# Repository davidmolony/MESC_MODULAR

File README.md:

# MESC_MODULAR
This is a repo for an experimental through hole stage and power driver

For use either with Pinski control board, or with any control stage - Lebowski, nucleo breakouts and jumper wires, Infineon breakout boards... whatever.

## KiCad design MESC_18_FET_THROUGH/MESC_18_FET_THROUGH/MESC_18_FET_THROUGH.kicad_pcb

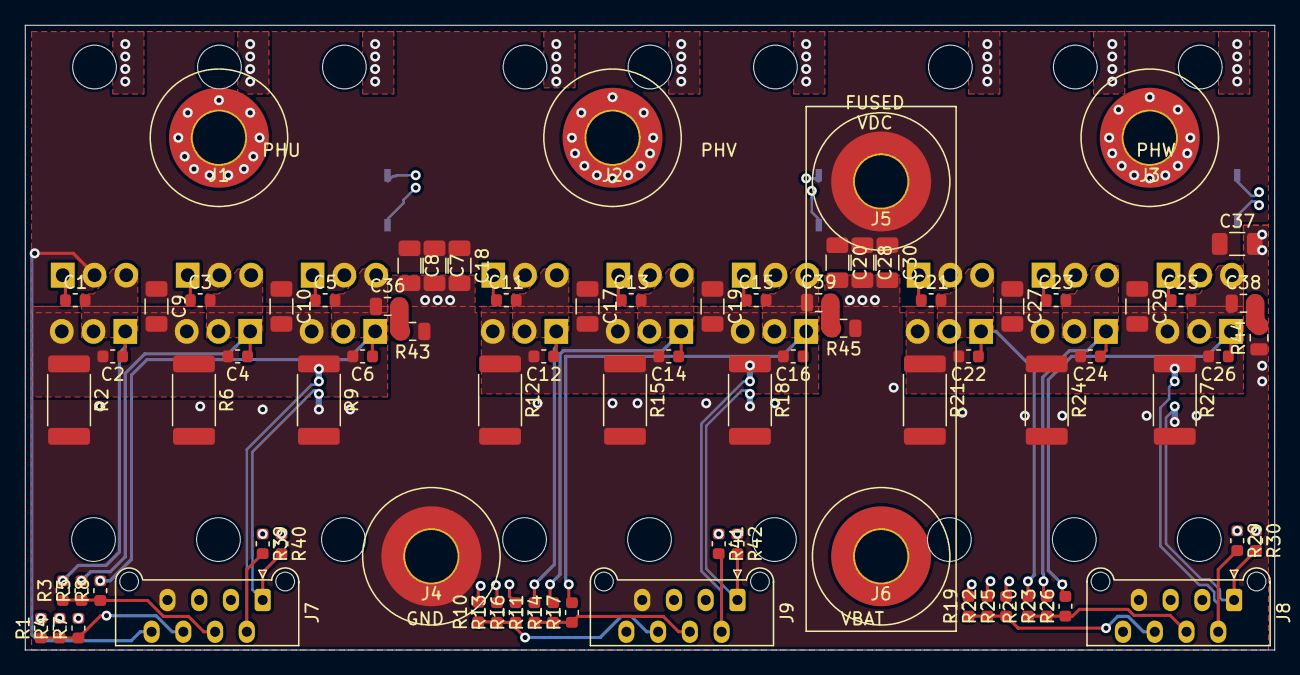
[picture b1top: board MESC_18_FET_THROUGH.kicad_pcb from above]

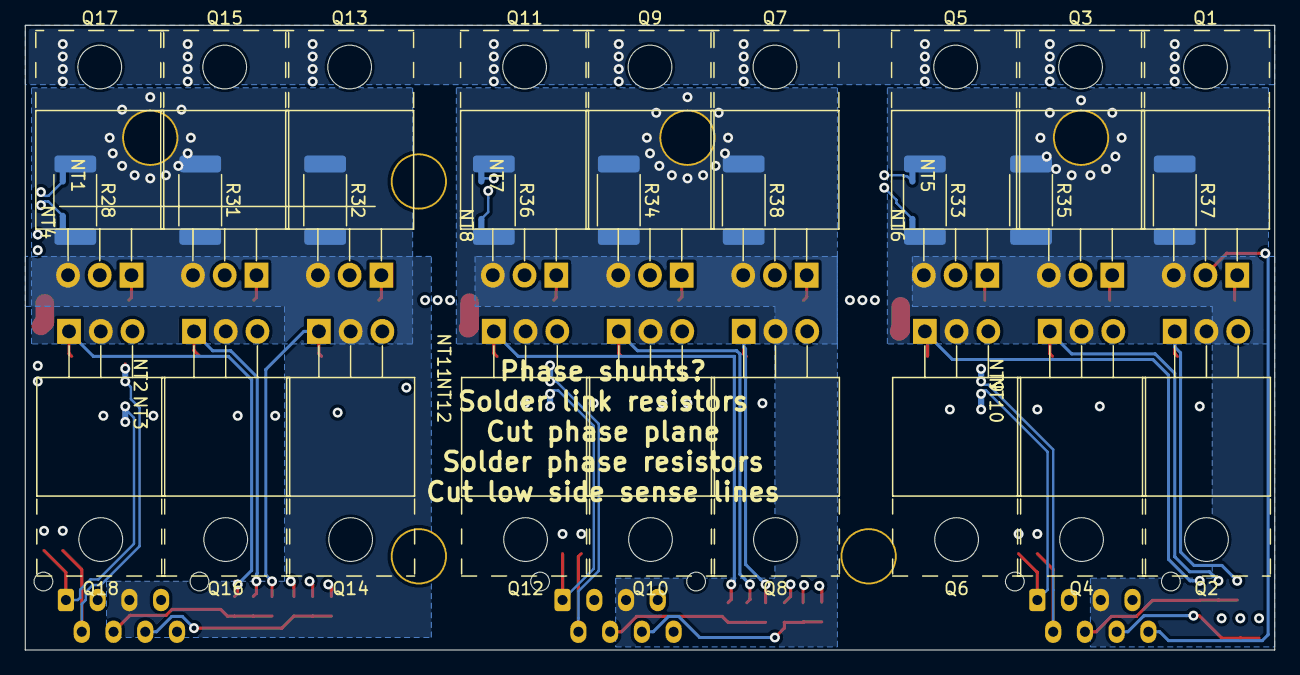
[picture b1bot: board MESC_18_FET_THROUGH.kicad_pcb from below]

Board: 4 copper layers, 100.0 x 50.0 mm, 118 parts (39 on the bottom side), 47 nets.

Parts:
C1, C2, C3, C4, C5, C6, C11, C12, C13, C14, C15, C16, C21, C22, C23, C24, C25, C26: DNF 4.7nF 25V; C_0603_1608Metric
C7, C8, C9, C10, C17, C18, C19, C20, C27, C28, C29, C30, C37: 1uF 100V; C_1206_3216Metric
C36, C38, C39: 4.7nF 100V; C_0805_2012Metric
J1, J2, J3, J4, J5, J6: M4 screw; Wuerth_Redcube_M4
J7, J8, J9: Conn_01x08_Male; Molex_Picoflex_90325-0008_2x04_P1.27mm_Vertical
NT1, NT2, NT3, NT4, NT5, NT6, NT7, NT8, NT9, NT10, NT11, NT12: Net-Tie_2; NetTie-2_SMD_Pad0.5mm
Q1, Q2, Q3, Q4, Q5, Q6, Q7, Q8, Q9, Q10, Q11, Q12, Q13, Q14, Q15, Q16, Q17, Q18: STP150N10F7; TO-220-3_Horizontal_TabUp
R1, R3, R4, R5, R7, R8, R10, R11, R13, R14, R16, R17, R19, R20, R22, R23, R25, R26: 4.7R; R_0603_1608Metric
R2, R6, R9, R12, R15, R18, R21, R24, R27, R28, R31, R32, R33, R34, R35, R36, R37, R38: 0R001; R_2512_6332Metric
R29, R30, R39, R40, R41, R42: DNF 100R; R_0603_1608Metric
R43, R44, R45: 2R2; R_0805_2012Metric

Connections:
+VDC: C7.1, C8.1, C9.1, C10.1, C17.1, C18.1, C19.1, C20.1, C27.1, C28.1, C29.1, C30.1, C37.1, J5.1, J7.8, Q1.2, Q3.2, Q5.2, Q7.2, Q9.2, Q11.2, Q13.2, Q15.2, Q17.2
/ISUH+: NT5.2, R39.1
/ISUH-: NT6.2, R40.1
/ISVH+: NT7.2, R41.1
/ISVH-: NT8.2, R42.1
/ISWH+: NT1.2, R29.1
/ISWH-: NT4.2, R30.1
GND: C7.2, C8.2, C18.2, C20.2, C28.2, C30.2, C37.2, J4.1, J7.7, J8.7, J9.7, NT3.2, NT10.2, NT12.2, R2.2, R6.2, R9.2, R12.2, R15.2, R18.2, R21.2, R24.2, R27.2, R43.1, R44.1, R45.1
ISU+: J7.2, NT9.2, R39.2
ISU-: J7.1, NT10.1, R40.2
ISV+: J9.2, NT11.2, R41.2
ISV-: J9.1, NT12.1, R42.2
ISW+: J8.2, NT2.2, R29.2
ISW-: J8.1, NT3.1, R30.2
unnamed: C1.1, Q1.1, R1.2
unnamed: C2.1, Q2.1, R3.2
unnamed: C3.1, Q3.1, R4.2
unnamed: C4.1, Q4.1, R5.2
unnamed: C5.1, Q5.1, R7.2
unnamed: C6.1, Q6.1, R8.2
unnamed: C11.1, Q7.1, R10.2
unnamed: C12.1, Q8.1, R11.2
unnamed: C13.1, Q9.1, R13.2
unnamed: C14.1, Q10.1, R14.2
unnamed: C15.1, Q11.1, R16.2
unnamed: C16.1, Q12.1, R17.2
unnamed: C21.1, Q13.1, R19.2
unnamed: C22.1, Q14.1, R20.2
unnamed: C23.1, Q15.1, R22.2
unnamed: C24.1, Q16.1, R23.2
unnamed: C25.1, Q17.1, R25.2
unnamed: C26.1, Q18.1, R26.2
unnamed: C36.2, R43.2
unnamed: C38.2, R44.2
unnamed: C39.2, R45.2
UGH: J7.6, R1.1, R4.1, R7.1
UGL: J7.4, R3.1, R5.1, R8.1
USOURCE: C2.2, C4.2, C6.2, C9.2, C10.2, J7.3, NT9.1, Q2.3, Q4.3, Q6.3, R2.1, R6.1, R9.1
USWITCH: C1.2, C3.2, C5.2, C36.1, J1.1, J7.5, NT5.1, NT6.1, Q1.3, Q2.2, Q3.3, Q4.2, Q5.3, Q6.2, R33.1, R33.2, R35.1, R35.2, R37.1, R37.2
VGH: J9.6, R10.1, R13.1, R16.1
VGL: J9.4, R11.1, R14.1, R17.1
VSOURCE: C12.2, C14.2, C16.2, C17.2, C19.2, J9.3, NT11.1, Q8.3, Q10.3, Q12.3, R12.1, R15.1, R18.1
VSWITCH: C11.2, C13.2, C15.2, C39.1, J2.1, J9.5, NT7.1, NT8.1, Q7.3, Q8.2, Q9.3, Q10.2, Q11.3, Q12.2, R34.1, R34.2, R36.1, R36.2, R38.1, R38.2
WGH: J8.6, R19.1, R22.1, R25.1
WGL: J8.4, R20.1, R23.1, R26.1
WSOURCE: C22.2, C24.2, C26.2, C27.2, C29.2, J8.3, NT2.1, Q14.3, Q16.3, Q18.3, R21.1, R24.1, R27.1
WSWITCH: C21.2, C23.2, C25.2, C38.1, J3.1, J8.5, NT1.1, NT4.1, Q13.3, Q14.2, Q15.3, Q16.2, Q17.3, Q18.2, R28.1, R28.2, R31.1, R31.2, R32.1, R32.2

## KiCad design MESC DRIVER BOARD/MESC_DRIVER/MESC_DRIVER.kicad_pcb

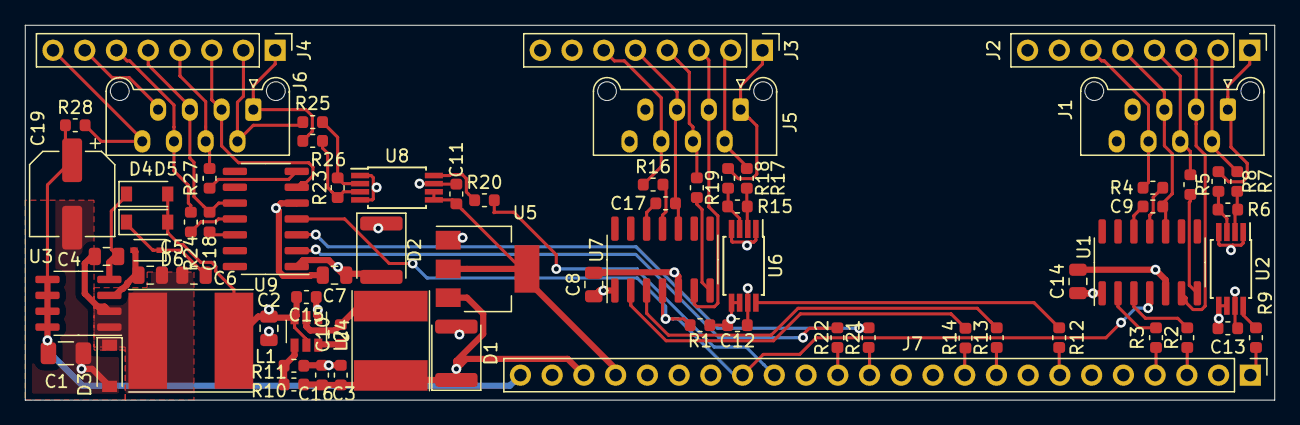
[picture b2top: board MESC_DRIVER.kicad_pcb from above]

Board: 4 copper layers, 100.0 x 30.0 mm, 71 parts (0 on the bottom side), 65 nets.

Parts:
C1: C_Small; C_1206_3216Metric
C2, C4, C5, C6, C7, C8, C14: C_Small; C_0805_2012Metric
C3, C9, C10, C11, C12, C13, C15, C16, C17, C18: C_Small; C_0603_1608Metric
C19: CP_Small; CP_Elec_6.3x7.7
D1, D2: D_TVS; D_1812_4532Metric
D3, D4, D5: D_Small; D_SOD-123
D6: D_Zener_Small; D_SOD-323
J1, J5, J6: Conn_01x08_Male; Molex_Picoflex_90325-0008_2x04_P1.27mm_Vertical
J2, J3, J4: Conn_01x08_Male; PinHeader_1x08_P2.54mm_Vertical
J7: Conn_01x24_Male; PinHeader_1x24_P2.54mm_Vertical
L1: L_Small; L_Taiyo-Yuden_NR-80xx_HandSoldering
L2: L_Small; L_Taiyo-Yuden_NR-60xx_HandSoldering
R1, R2, R3, R4, R5, R6, R7, R8, R9, R10, R11, R12, R13, R14, R15, R16, R17, R18, R19, R20, R21, R22, R23, R24, R25, R26, R27, R28: R_Small; R_0603_1608Metric
U1, U7, U9: 2EDL23N06; SOIC-14_3.9x8.7mm_P1.27mm
U2, U6, U8: INA240A2PW; TSSOP-8_4.4x3mm_P0.65mm
U3: VIPer22AS; SOIC-8_3.9x4.9mm_P1.27mm
U4: TPS563200; SOT-23-6
U5: LM1117-3.3; SOT-223-3_TabPin2

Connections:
+3V3: C11.1, C12.1, C13.1, J7.21, R1.2, U2.5, U2.6, U5.2, U6.5, U6.6, U8.5, U8.6
+5V: C3.1, C16.1, D1.1, J7.22, L2.1, R10.1, U5.3
+15V: C2.1, C7.1, C8.1, C14.1, C15.2, D2.2, D4.2, D5.2, J7.23, L1.1, U1.1, U4.3, U4.5, U7.1, U9.1
+BATT: J4.8, J6.8, R28.2
+VDC: C1.1, C19.1, J7.24, R28.1, U3.5, U3.6, U3.7, U3.8
GND: C1.2, C2.2, C3.2, C7.2, C8.2, C11.2, C12.2, C13.2, C14.2, C15.1, C16.2, C19.2, D1.2, D2.1, D3.2, J4.7, J6.7, J7.2, J7.8, J7.15, J7.20, R11.2, U1.5, U2.1, U2.4, U2.7, U4.1, U5.1, U6.1, U6.4, U6.7, U7.5, U8.1, U8.4, U8.7, U9.5
HINU: J7.4, R3.2
HINV: J7.10, R14.2
HINW: J7.14, R22.2
HOU: J1.6, J2.6, R4.1
HOV: J3.6, J5.6, R16.1
HOW: J4.6, J6.6, R24.1
IU+: J1.2, J2.2, R7.2
IU-: J1.1, J2.1, R8.1
IV+: J3.2, J5.2, R17.2
IV-: J3.1, J5.1, R18.1
IW+: J4.2, J6.2, R25.2
IW-: J4.1, J6.1, R26.1
LINU: J7.3, R2.1
LINV: J7.9, R13.1
LINW: J7.13, R21.1
LOU: J1.4, J2.4, R5.1
LOV: J3.4, J5.4, R19.1
LOW: J4.4, J6.4, R27.1
unnamed: C4.1, D4.1, U3.4
unnamed: C4.2, C5.2, C6.2, D3.1, L1.2, U3.1, U3.2
unnamed: C6.1, D5.1, D6.1
unnamed: C9.1, U1.12
unnamed: C10.1, U4.6
unnamed: C10.2, L2.2, U4.2
unnamed: C17.1, U7.12
unnamed: C18.1, U9.12
unnamed: R2.2, U1.3
unnamed: R3.1, U1.2
unnamed: R4.2, U1.11
unnamed: R5.2, U1.7
unnamed: R6.1, R8.2, U2.3
unnamed: R6.2, R7.1, U2.2
unnamed: R9.1, U2.8
unnamed: R10.2, R11.1, U4.4
unnamed: R12.1, U6.8
unnamed: R13.2, U7.3
unnamed: R14.1, U7.2
unnamed: R15.1, R18.2, U6.3
unnamed: R15.2, R17.1, U6.2
unnamed: R16.2, U7.11
unnamed: R19.2, U7.7
unnamed: R20.1, U8.8
unnamed: R21.2, U9.3
unnamed: R22.1, U9.2
unnamed: R23.1, R26.2, U8.3
unnamed: R23.2, R25.1, U8.2
unnamed: R24.2, U9.11
unnamed: R27.2, U9.7
OPUout: J7.1, R9.2
OPVout: J7.7, R12.2
OPWout: J7.16, R20.2
PGU: J1.3, J2.3, U1.6
PGV: J3.3, J5.3, U7.6
PGW: J4.3, J6.3, U9.6
SWU: C9.2, J1.5, J2.5, U1.10
SWV: C17.2, J3.5, J5.5, U7.10
SWW: C18.2, J4.5, J6.5, U9.10
ViperFB: C5.1, D6.2, U3.3
nFAULT: J7.17, R1.1, U1.4, U7.4, U9.4

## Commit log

2021-05-16 Initial commit of 18 FET power and driver board
2021-05-16 Add DC bus voltage output to power board.
